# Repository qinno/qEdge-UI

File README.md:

# qEdge-UI

# Update
qEdge-UI supports now PICO2-W plattform (RP2350) with minimum changes as qEdge-UI++. Compilation now works in the Arduino 2.x.x IDE. LittleFS upload does not work in the moment, copy the files in /data to the SD-card, system copies it automagically to LittleFS on the first start. 

# About

This project is an example of use of what can be achieved with free/libre and open source software and free/libre and open source tools in a professional proceeding. 
In contrast to the generally accepted approach of commercial companies, the development results of this project (hardware and mechanical design, as well as software source code) are also available under an open source licence.

Based on the Raspberry Pi Pico (2), we have created a design that can be used as a starting point for further development. In order to keep things as simple as possible we use the Arduino platform.

Key hardware features of **qEdge-UI (qEdge-UI++)**:

- Raspberry Pi Pico RP2040 (2350)
- Dual-Core ARM Cortex M0+ CPU @133 MHz (ARM Cortex M33 @150 MHz or RISC-V)
- 264KB SRAM and 2MB Flash (520 KB / 4MB)
- WiFi + Bluetooth (Pico-W/Pico2-W)
- USB interface and power supply
- additional 12/24 VDC supply
- 3,2" TFT-Display 320x240 with resistive touch
- 4x1 keypad
- expansion connector for UART, I²C, GPIO, ADC
- RS-485 Interface
- Micro-SD-card slot
- LoRa module with stable SMA connector
- RTC with ultracap buffer
- Buzzer
- RGB-LEDs for signalling
- Raspberry Pi 3b/4b connectable (optional, not tested)

# Getting Started

### Electronics

To get started you will need the qEdge-UI electronic boards (main and display adapter). [We provide the full KiCad project here.](Electronics)

### Software

To get started with the software development you need a PC with:

* preinstalled Windows 7 or newer (64Bit), Linux (32/64Bit) or MacOS 10.10 newer
* An Arduino IDE 1.8.x including USB Driver support
* Addional you can use our qEdge-UI examples and libraries as a starting point for your own software development or you can download the precompiled UFS binaries of our qEdge-UI examples. [Here](Software) you can find the sources and installation guideline.

### Mechanics

To create the nice looking electronic box above you need a 3D printer [and the mechanics](Mechanics)

## qEdge-UI Hardware Test App functionality

The main objective of the qEdge-UI HwTestApp software is to check the functionality of the hardware.

* Touch - check precision of touch screen
* Slideshow - show PNG files on SD-Card (micro)
* UART - Test UART1 (RX/TX)
* RS-485 - Test UART2 connected to RS-485 driver (RX/TX)
* Micro-SD-card - check SD-card presence and list files on SD-card
* LittleFS - list, copy, rename and delete files in the filesystem
* LoRa - send/receive LoRa messages
* WiFi - scan and log in a network for receiving NTP time information
* GAME - space shooters clone to show performance
* Info - show system infos
* Keyboard - keyboard emulation
* Settings - set RGB preferences and backlight, test Buzzer

# Roadmap

See the [open issues](https://github.com/qinno/qEdge-UI/issues) for a list of proposed features (and known issues).

# Contributing

First of all, thank you for taking the time to contribute! Contributions are what make the open source community such an amazing place to learn, inspire and create. Every contribution you make benefits everyone else and is **greatly appreciated**.

Please try to create bug reports that are:

- _Reproducible._ Include steps to reproduce the problem.
- _Specific._ Include as much detail as possible: which version, what environment, etc.
- _Unique._ Do not duplicate existing open issues.
- _Scoped to a Single Bug._ One bug per report.

# Use and Regulations

Please note that this is an engineering example and is not certified to European regulations such as CE and RED, so use it at your own risk. If you find this platform helpful, we can assist you in creating a production-ready and certified product.

# Known limitations

This project is at the moment not used in a commercial open source product, but can be used as a starting point for that purpose. Please fell free to contact us for more information.

# Support

Reach out to the maintainer at one of the following places:

- By email which is located at [qinno GmbH · GitHub](https://github.com/qinno)

# Licenses

This project is licensed under the following open source licenses:
* Electronics are under [**CERN-OHL-S V2**](https://ohwr.org/cern_ohl_s_v2.txt)
* Mechanics and Design are under [**CC-BY-NC-4.0**](https://creativecommons.org/licenses/by-nc/4.0/legalcode)
* Software Examples are under [**GPLv3**](https://www.gnu.org/licenses/gpl-3.0.en.html)
   
See corresponding Readme.md files in the folders Electronics, Mechanics and Software for more detailed information.

[Raspberry Pi is a trademark of Raspberry Pi Ltd](http://www.raspberrypi.com/)

# Acknowledgements

Thanks to our partners supporting this project:

* [Our Customer Varmeco for the generous donation of material](https://varmeco.de)

* Axel Isele for the mechanics design

* [Würth Elektronik for free samples for the very first prototypes](https://www.we-online.com/de)

* All qinno-colleagues for their commitment even in their spare time

Thanks also for these awesome resources that were used during the development of the **qEdge-UI**:

* [The KiCAD team for their great CAE tool](https://www.kicad.org/)
* [Earle F. Philhower, III for his Arduino library for the RP2040](https://github.com/earlephilhower/arduino-pico)
* [Bodmer for his versatile TFT-Library](https://github.com/Bodmer/TFT_eSPI)
* [Larry Bank for his PNG extension](https://github.com/bitbank2/PNGdec)
* [The Adafruit Industries Team for their RGB-LED library](https://github.com/adafruit/Adafruit_NeoPixel)
* [The Arduino team for their easy to use (now legacy) IDE](https://www.arduino.cc/en/software)
* [Sandeep Mistry for his handy LoRa library](https://github.com/sandeepmistry/arduino-LoRa)

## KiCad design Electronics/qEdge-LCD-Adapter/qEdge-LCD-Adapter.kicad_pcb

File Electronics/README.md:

# qEdge-UI electronics

In this directory you will find the complete electronic design in KiCAD.

### The main electronics

[in the directory qedge-UI](qEdge-UI)

### The display adapter board

 [in the directory qEdge-LCD-Adapter](qEdge-LCD-Adapter)

You need to glue the display to the adapter board with double-sided adhesive tape and connect it to the ZIF-connector.

For use with RaspBerry Pi Pico or Pico-W you need to close the Jumpers JP500 and JP501. After you have assembled both boards, you need to connect them with a ribbon cable.

Now screw the LCD display on top of the main board.

You can supply the unit via Micro-USB (5V) and/or via the Phoenix connectors with 12V/24V (mating connector Phoenix 1952267).

The RS-485 connector needs Phoenix mating connector 1952270 to fit.

Fingers crossed ...

# License

(C) 2023 qinno - this work is licensed under CERN-OHL-S
see https://ohwr.org/cern_ohl_s_v2.pdf for more information

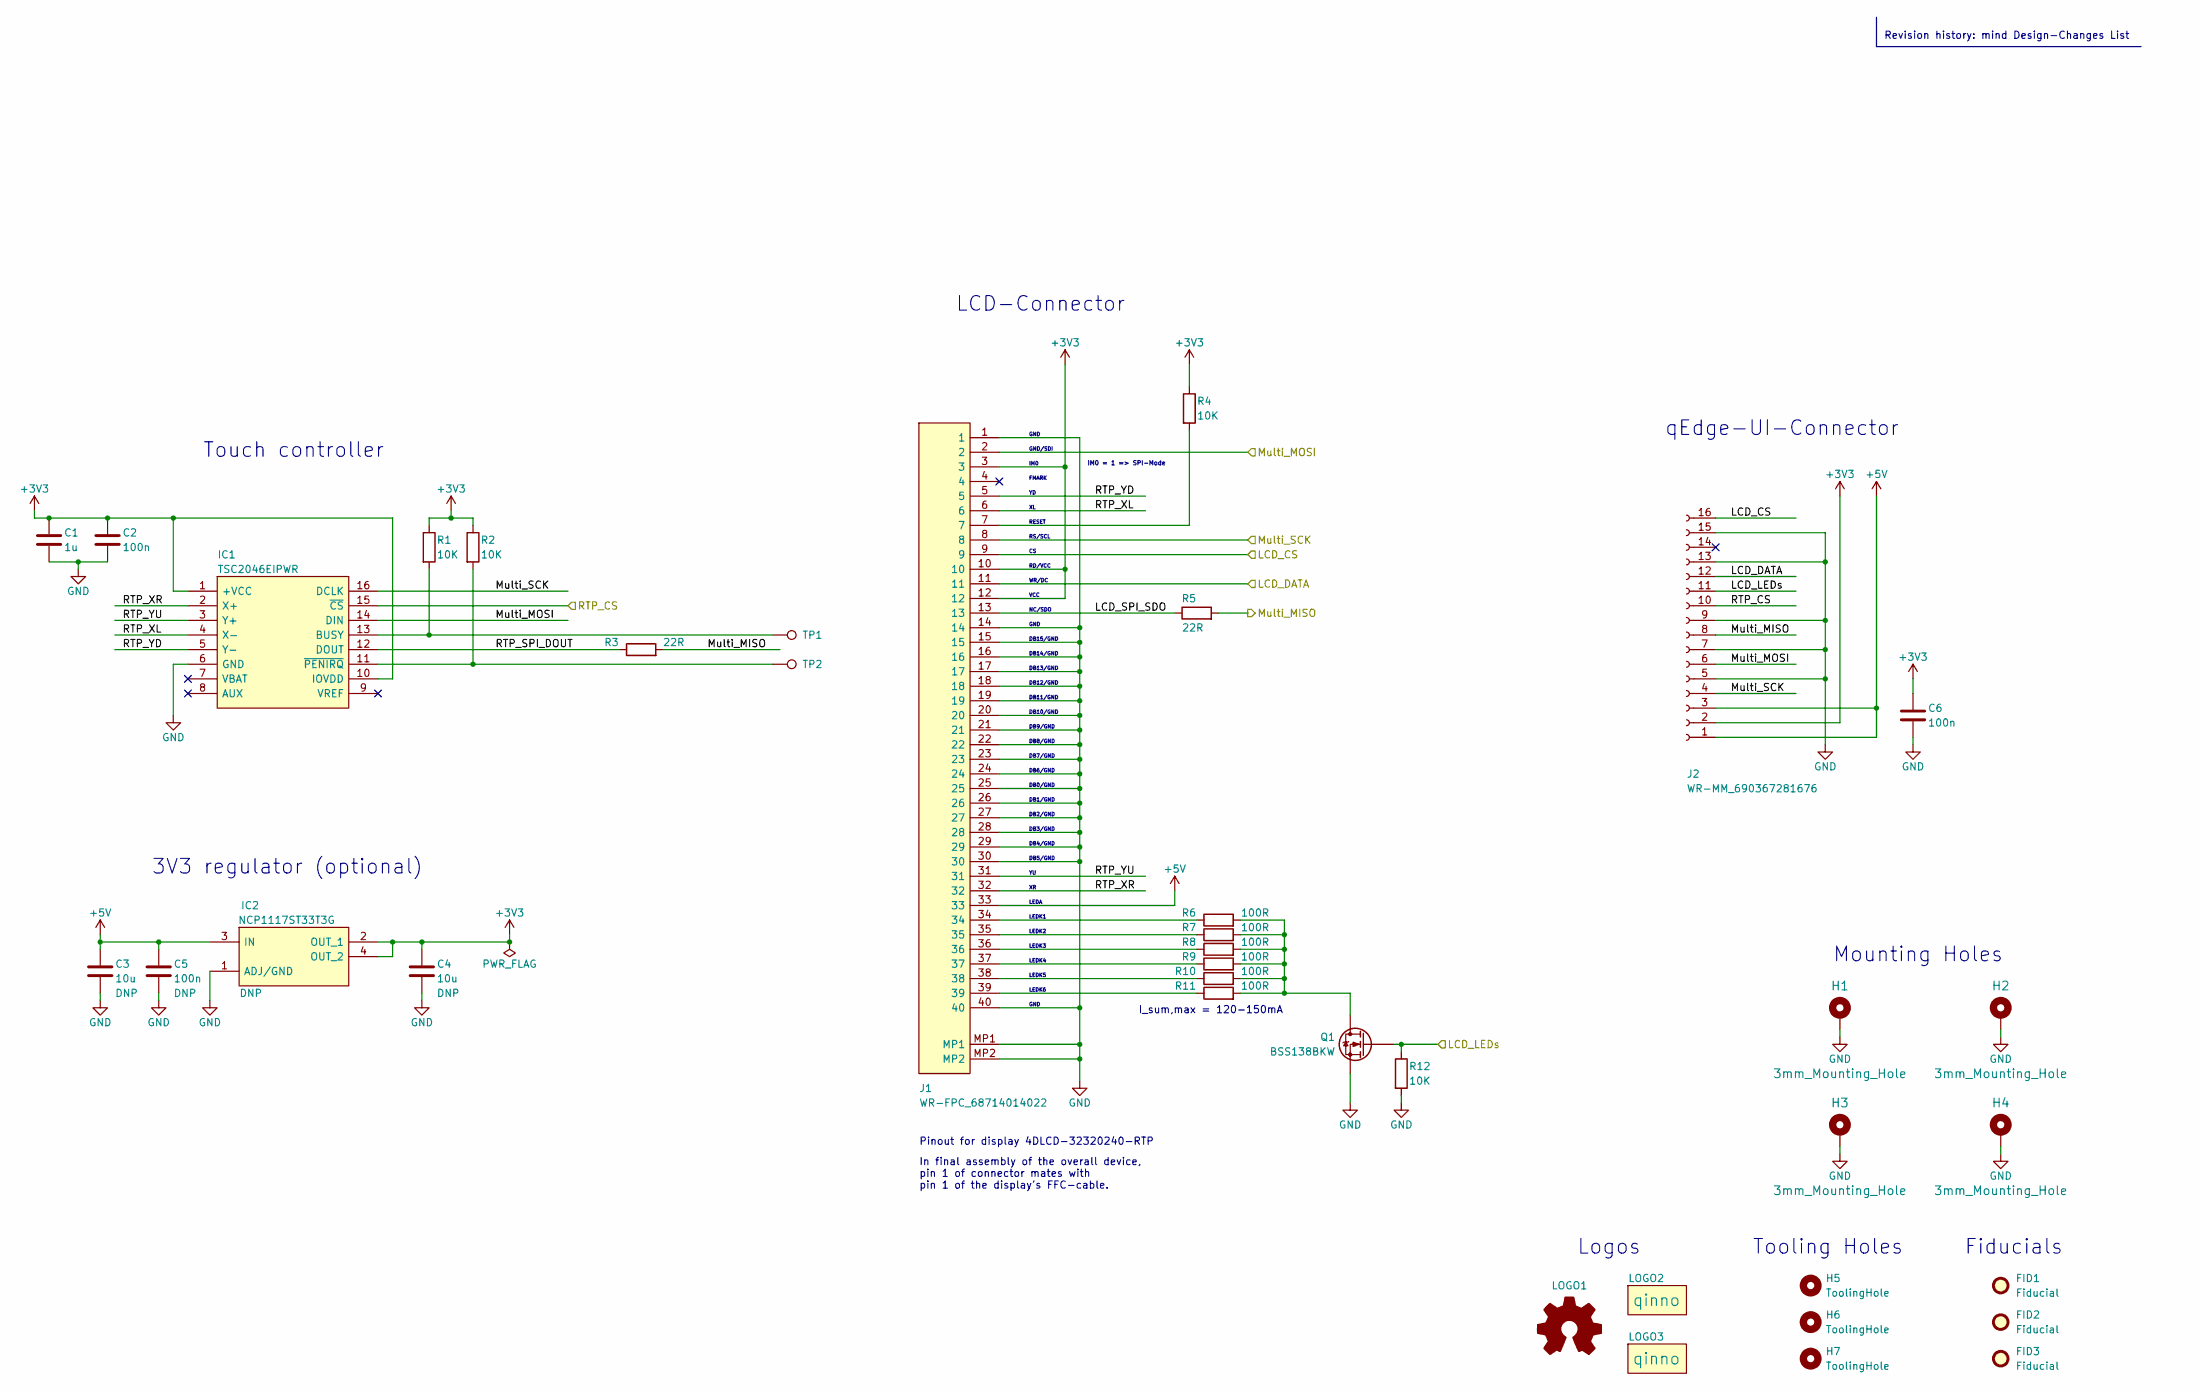
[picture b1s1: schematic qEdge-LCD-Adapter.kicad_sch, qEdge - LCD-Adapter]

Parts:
C1: 1u; C_0603_1608Metric
C2, C5, C6: 100n; C_0603_1608Metric
C3, C4: 10u; C_0603_1608Metric
FID1, FID2, FID3: Fiducial; Fiducial_1mm_Mask3mm
H1, H2, H3, H4: 3mm_Mounting_Hole; MountingHole_3.2mm_M3_DIN965_Pad
H5, H6, H7: ToolingHole; JLCSMT_ToolingHole
IC1: TSC2046EIPWR; SOP65P640X120-16N; Manufacturer_Part_Number TSC2046EIPWR
IC2: NCP1117ST33T3G; SOT230P700X180-4N; Manufacturer_Part_Number NCP1117ST33T3G
J1: WR-FPC_68714014022; Wuerth_WR-FPC_68714014022; Manufacturer_Part_Number 68714014022
J2: WR-MM_690367281676; Wuerth_WR-MM_690367281676; Manufacturer_Part_Number 690367281676
LOGO1: Logo_Open_Hardware_Small; OSHW-Logo2_9.8x8mm_Copper
LOGO2, LOGO3: qinno; Logo-qinno-2
Q1: BSS138BKW; SOT-323_SC-70; Manufacturer_Part_Number BSS138BKW,115
R1, R2, R4, R12: 10K; R_0603_1608Metric
R3, R5: 22R; R_0603_1608Metric
R6, R7, R8, R9, R10, R11: 100R; R_0603_1608Metric
TP1, TP2: TestPoint; TestPoint_Pad_D1.0mm

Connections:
+3V3: C1.1, C2.1, C4.1, C6.1, IC1.1 (+VCC), IC1.10 (IOVDD), IC2.2 (OUT_1), IC2.4 (OUT_2), J1.3, J1.10, J1.12, J2.2, R1.1, R2.1, R4.1
+5V: C3.1, C5.1, IC2.3 (IN), J1.33, J2.1, J2.3
/LCD_CS: J1.9, J2.16
/LCD_DATA: J1.11, J2.12
/LCD_LEDs: J2.11, Q1.1 (G), R12.1
/LCD_SPI_SDO: J1.13, R5.1
/Multi_MISO: J2.8, R3.2, R5.2
/Multi_MOSI: IC1.14 (DIN), J1.2, J2.6
/Multi_SCK: IC1.16 (DCLK), J1.8, J2.4
/RTP_CS: IC1.15 (~CS), J2.10
/RTP_SPI_DOUT: IC1.12 (DOUT), R3.1
/RTP_XL: IC1.4 (X-), J1.6
/RTP_XR: IC1.2 (X+), J1.32
/RTP_YD: IC1.5 (Y-), J1.5
/RTP_YU: IC1.3 (Y+), J1.31
GND: C1.2, C2.2, C3.2, C4.2, C5.2, C6.2, H1.1, H2.1, H3.1, H4.1, IC1.6 (GND), IC2.1 (ADJ/GND), J1.1, J1.14, J1.15, J1.16, J1.17, J1.18, J1.19, J1.20, J1.21, J1.22, J1.23, J1.24, J1.25, J1.26, J1.27, J1.28, J1.29, J1.30, J1.40, J1.MP1, J1.MP2, J2.5, J2.7, J2.9, J2.13, J2.15, Q1.2 (S), R12.2
unnamed: IC1.11 (~PENIRQ), R2.2, TP2.1
unnamed: IC1.13 (BUSY), R1.2, TP1.1
unnamed: J1.7, R4.2
unnamed: J1.34, R6.1
unnamed: J1.35, R7.1
unnamed: J1.36, R8.1
unnamed: J1.37, R9.1
unnamed: J1.38, R10.1
unnamed: J1.39, R11.1
unnamed: Q1.3 (D), R6.2, R7.2, R8.2, R9.2, R10.2, R11.2

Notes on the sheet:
LEDK3
GND
DB3/GND
DB9/GND
LEDK4
DB14/GND
LEDK2
DB5/GND
WR/DC
FMARK
Tooling Holes
IM0
LEDA
Pinout for display 4DLCD-32320240-RTP
RS/SCL
DB1/GND
LEDK5
RESET
DB10/GND
RD/VCC
DB8/GND
NC/SDO
DB0/GND
LEDK1
I_sum,max = 120-150mA
LEDK6
Logos
DB2/GND
DB11/GND
DB4/GND
qEdge-UI-Connector
DB7/GND
DB13/GND
LCD-Connector
DB15/GND
3V3 regulator (optional)
GND/SDI
Mounting Holes
Revision history: mind Design-Changes List
Touch controller

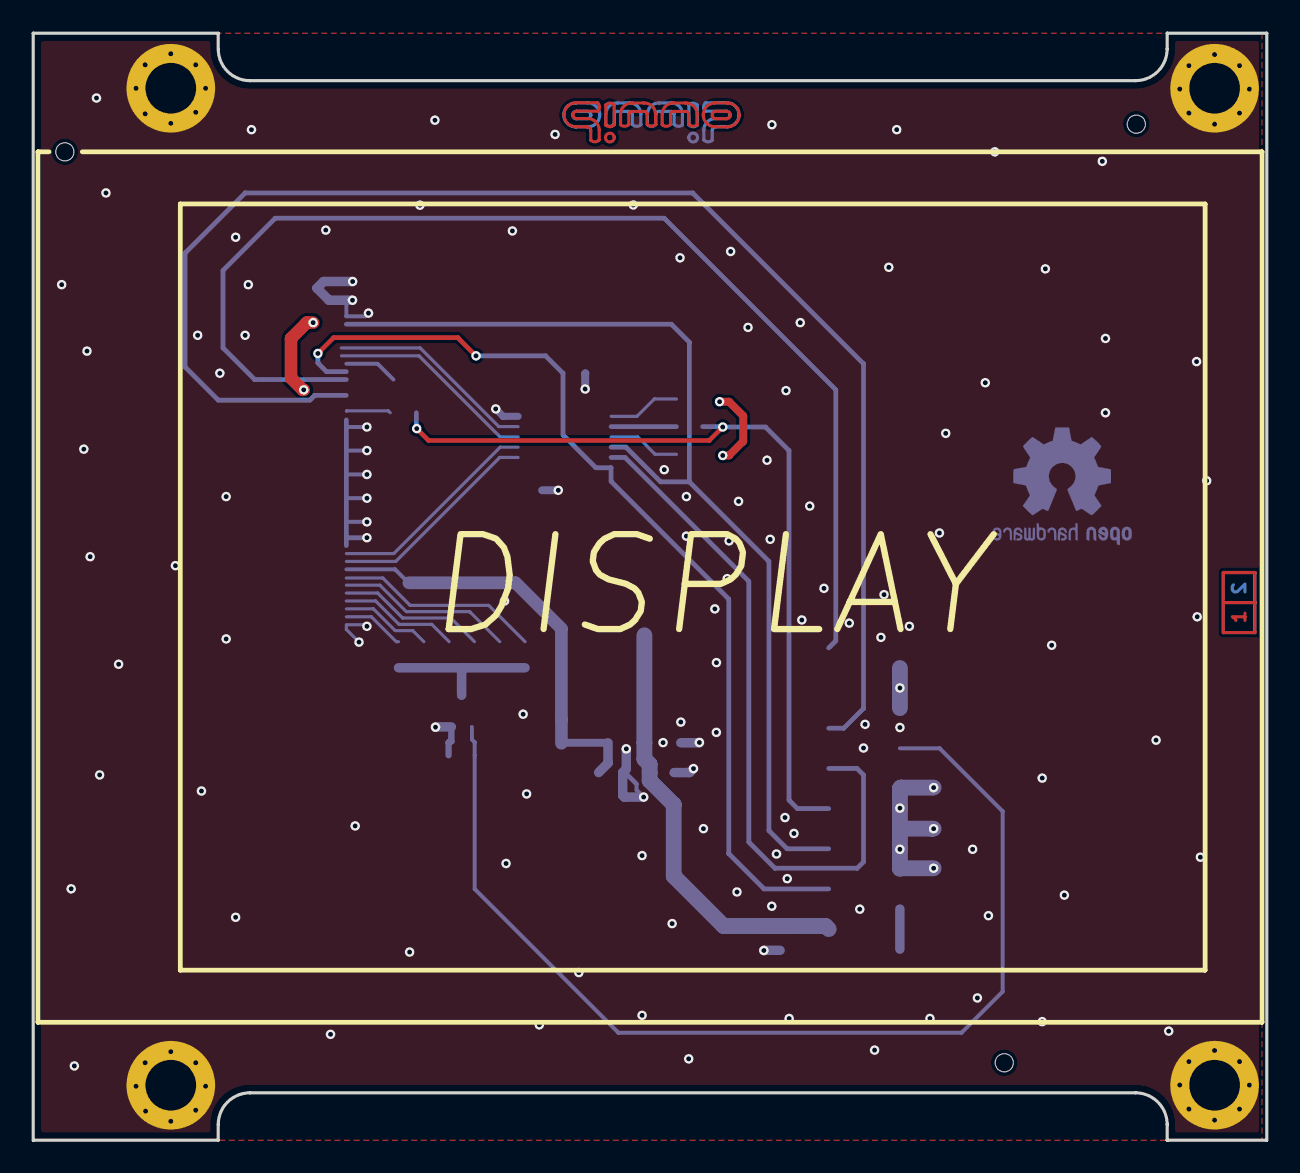
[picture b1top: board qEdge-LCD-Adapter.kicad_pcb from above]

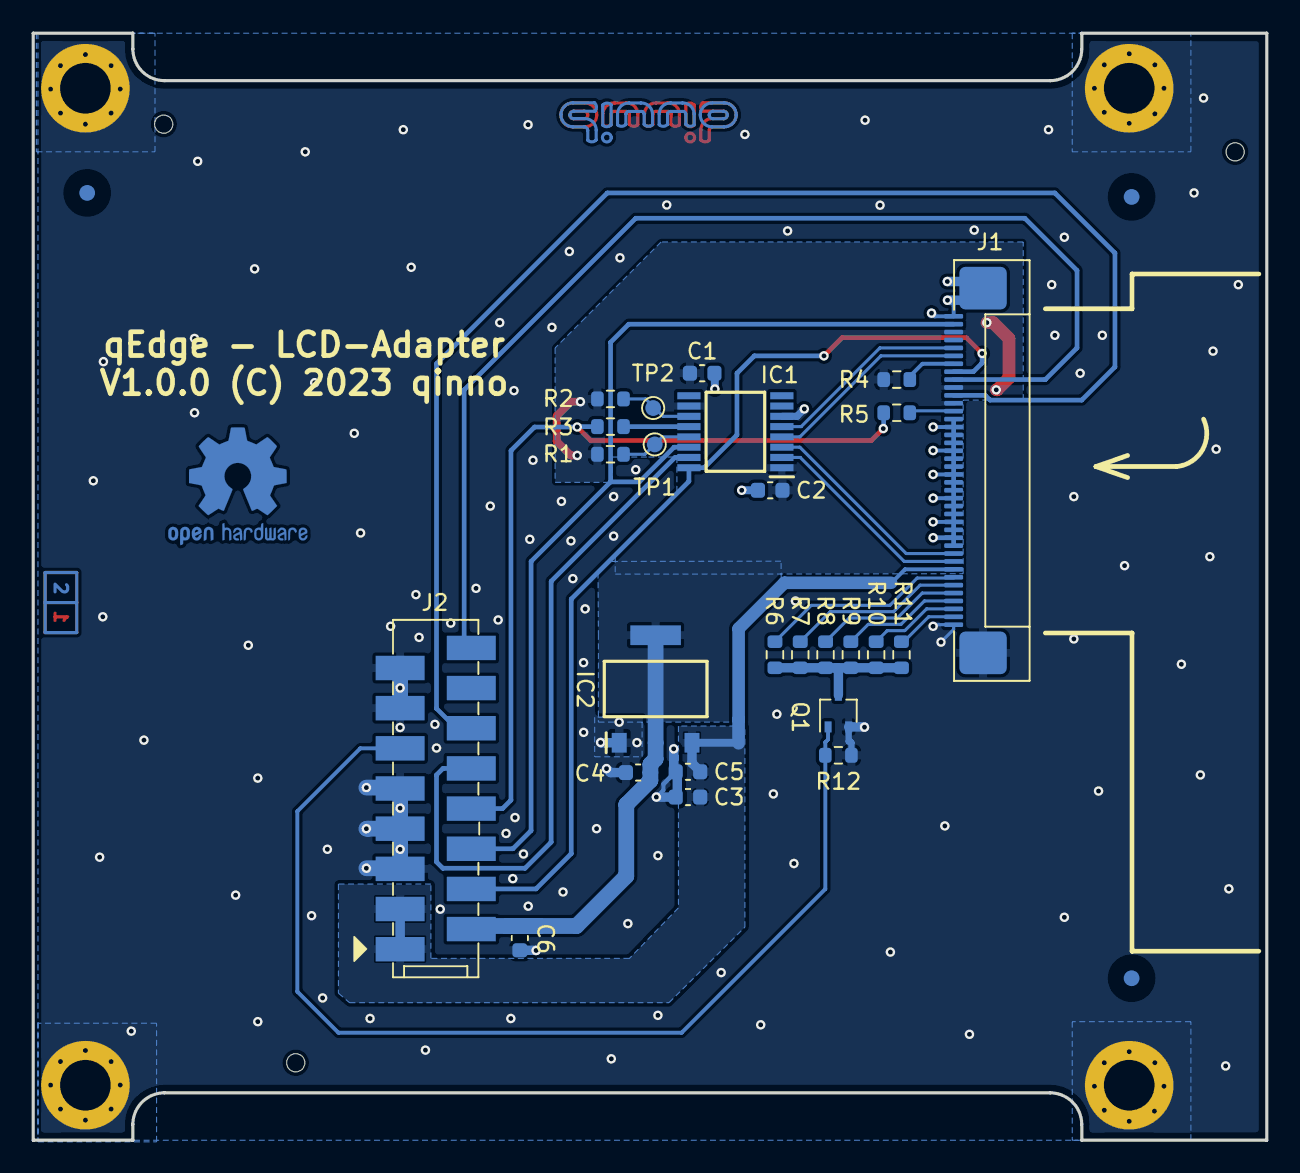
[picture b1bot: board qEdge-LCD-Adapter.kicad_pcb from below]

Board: 2 copper layers, 78.0 x 70.0 mm, 38 parts (30 on the bottom side), 26 nets.

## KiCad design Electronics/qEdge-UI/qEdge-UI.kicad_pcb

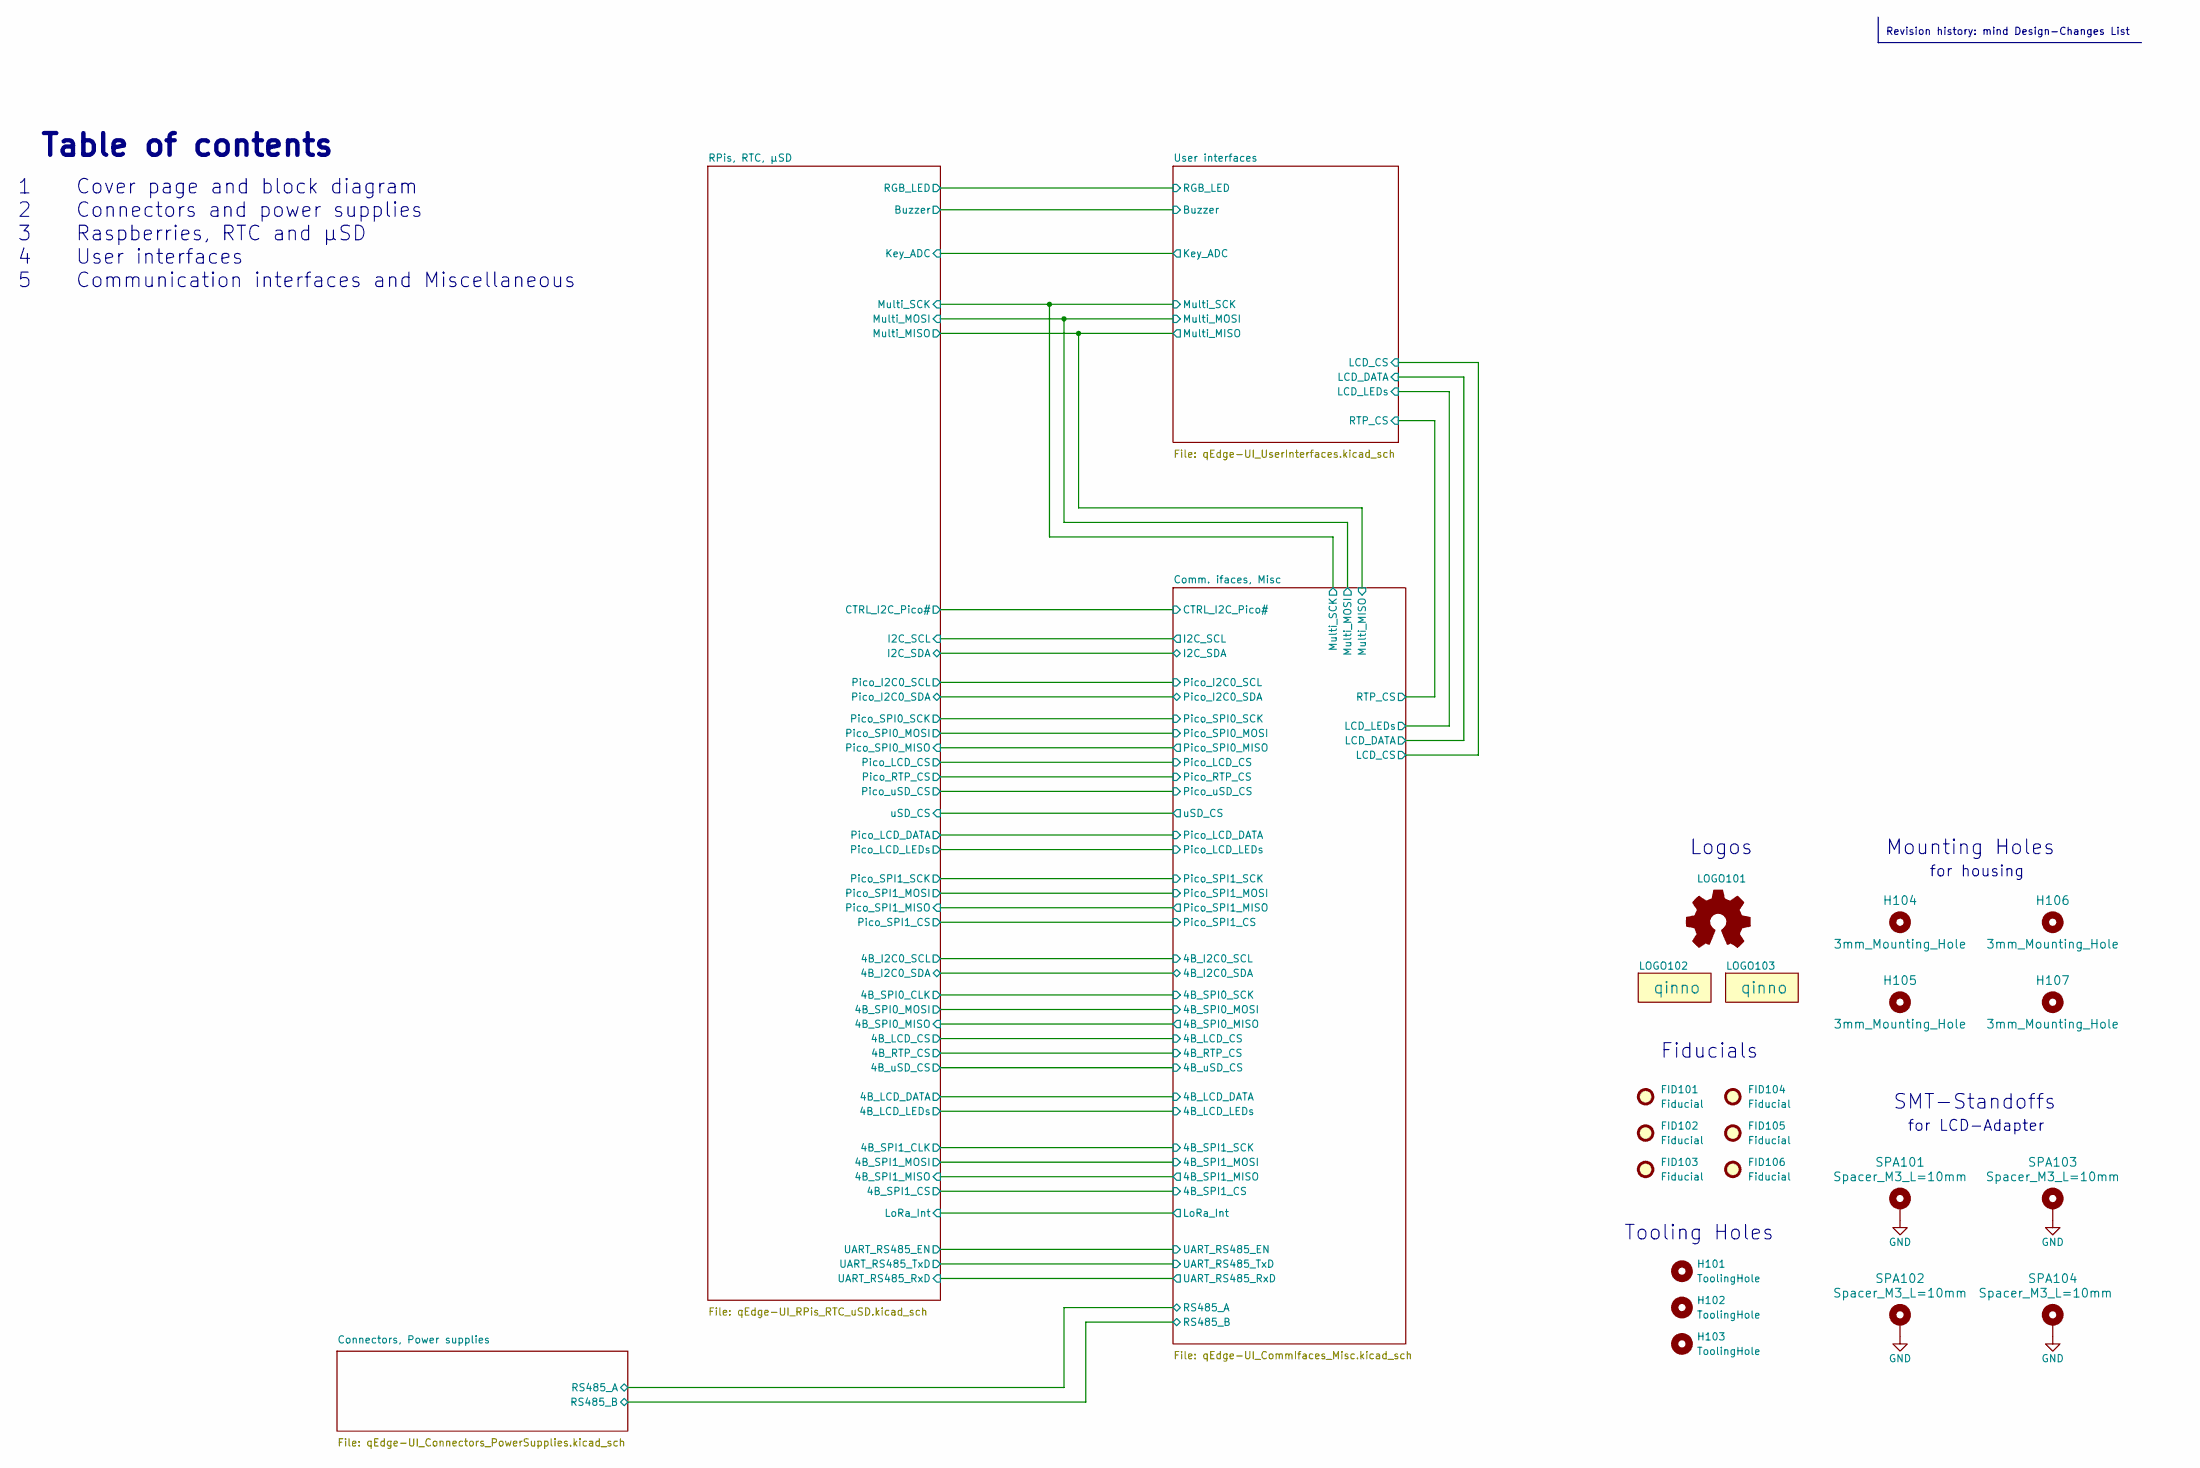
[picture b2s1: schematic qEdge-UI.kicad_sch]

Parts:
FID101, FID102, FID103, FID104, FID105, FID106: Fiducial; Fiducial_1mm_Mask3mm
H101, H102, H103: ToolingHole; JLCSMT_ToolingHole
H104, H105, H106, H107: 3mm_Mounting_Hole; NPTH_3mm_ID
LOGO101: Logo_Open_Hardware_Small; OSHW-Logo2_9.8x8mm_Copper
LOGO102, LOGO103: qinno; Logo-qinno-2
SPA101, SPA102, SPA103, SPA104: Spacer_M3_L=10mm; Mounting_Wuerth_WA-SMSI-M3_H10mm_9774100360; Manufacturer_Part_Number 9774100360

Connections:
GND: SPA101.1, SPA102.1, SPA103.1, SPA104.1; also elsewhere on the board

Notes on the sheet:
Logos
Mounting Holes
SMT-Standoffs
Tooling Holes
Revision history: mind Design-Changes List
for LCD-Adapter
Table of contents
for housing
1 Cover page and block diagram 2 Connectors and power supplies 3 Raspberries, RTC and µSD 4 User interfaces 5 Communication interfaces and Miscellaneous
Fiducials

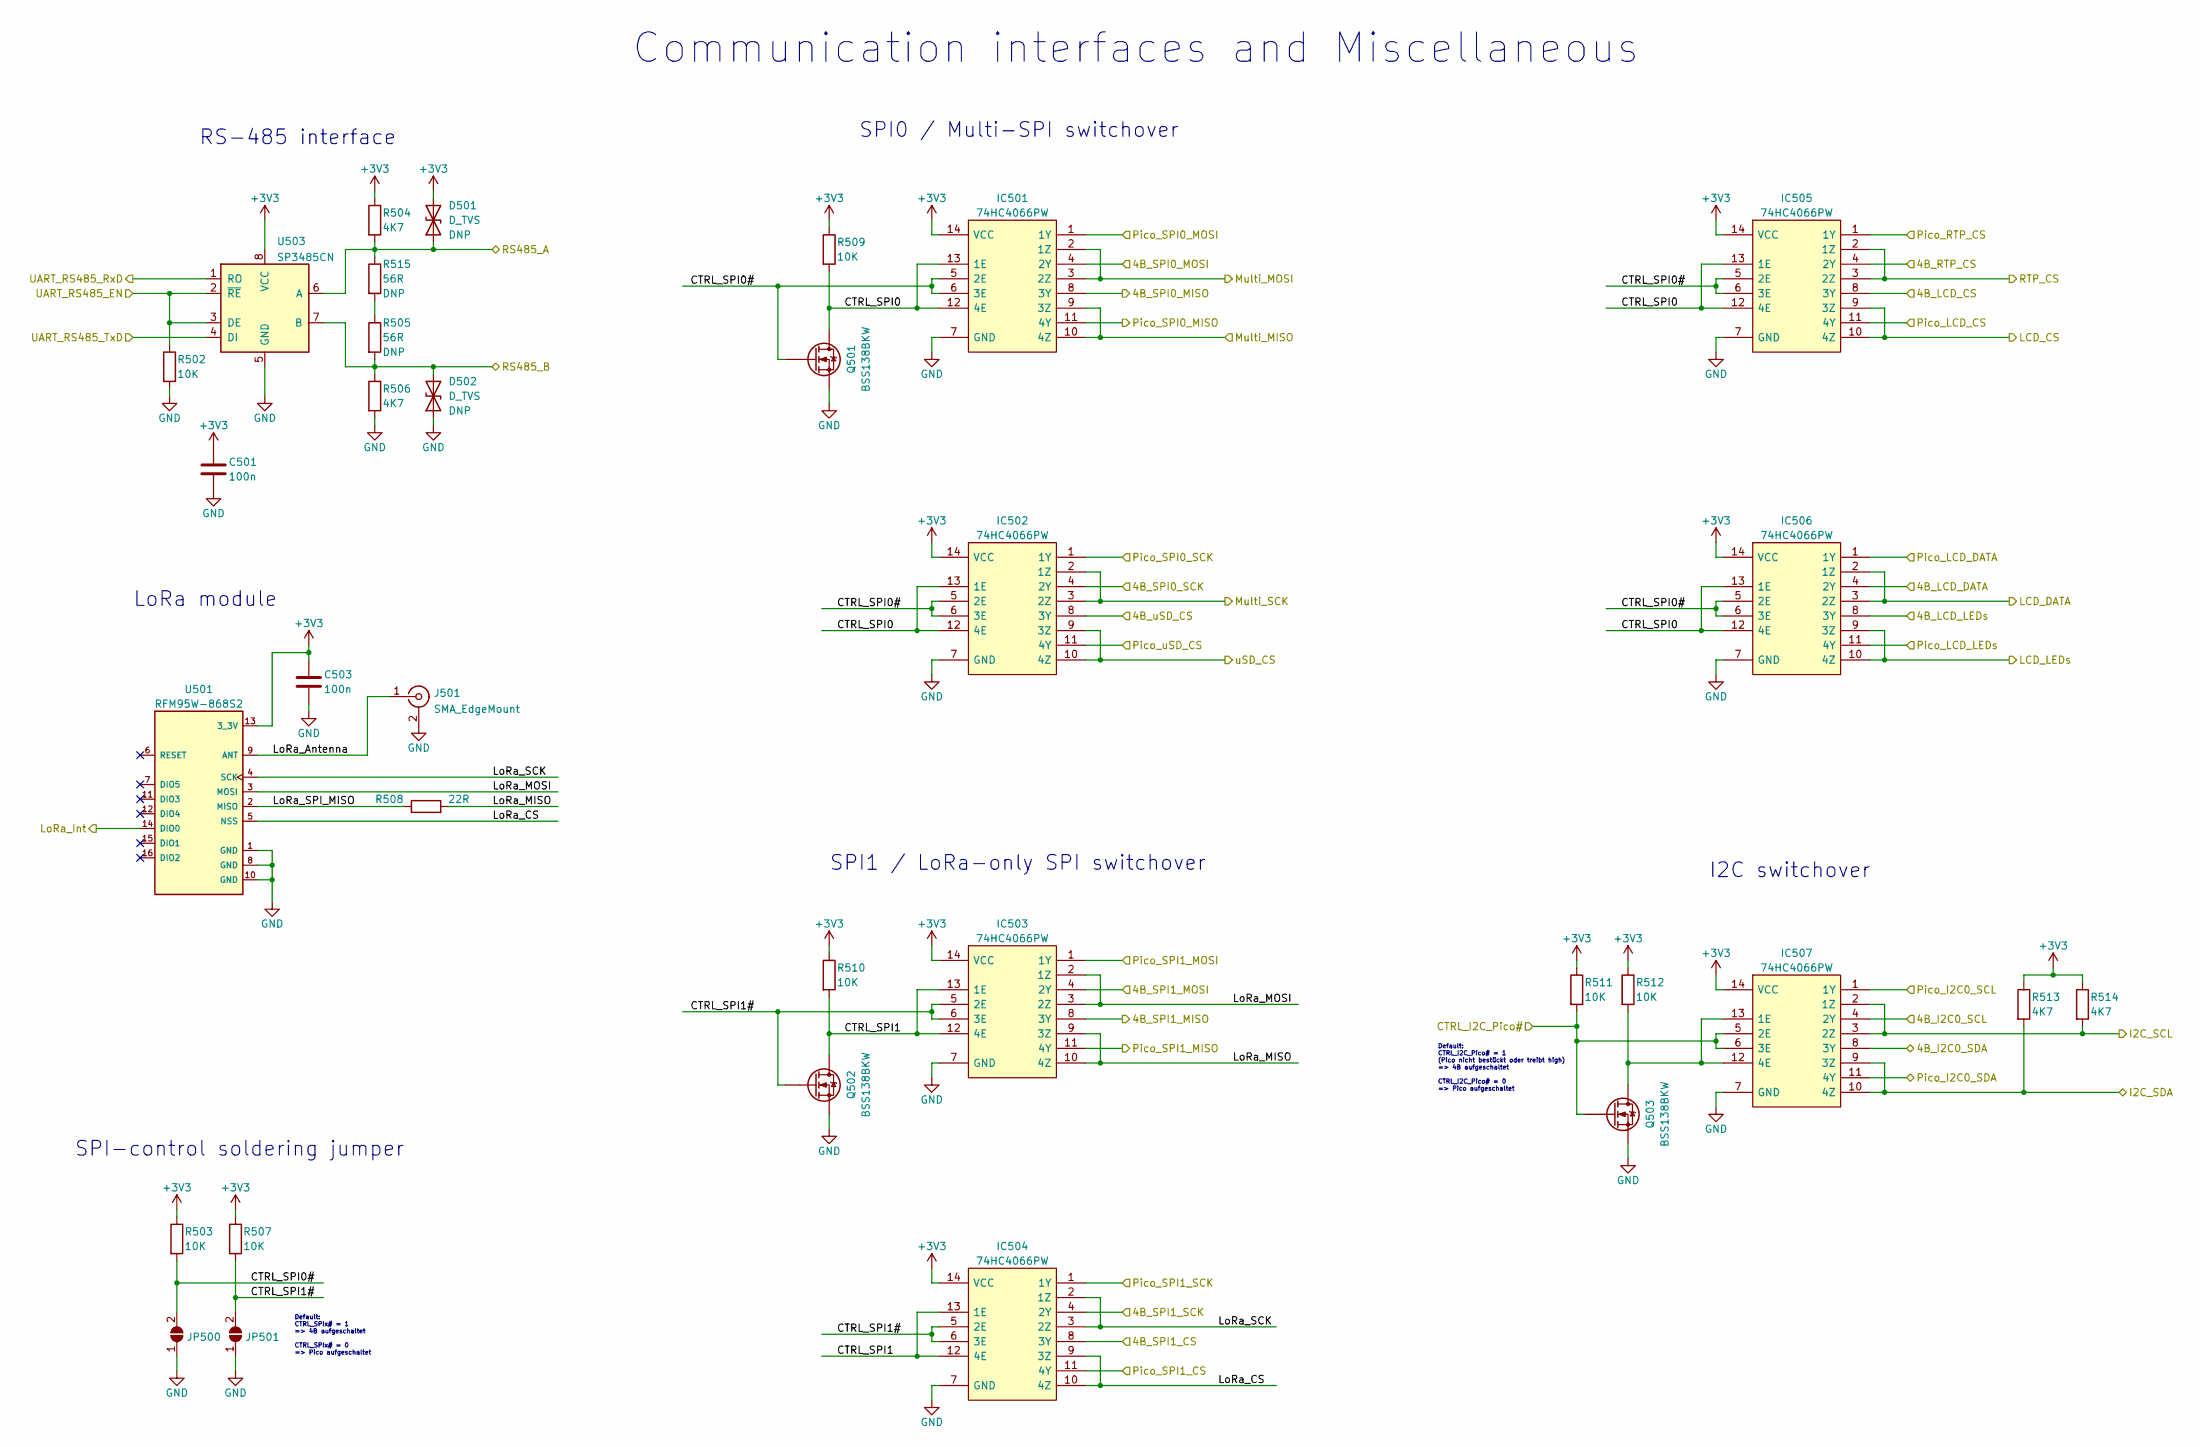
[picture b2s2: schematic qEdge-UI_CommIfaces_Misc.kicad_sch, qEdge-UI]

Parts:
C501, C503: 100n; C_0603_1608Metric
D501, D502: D_TVS; D_SMA_bipolar
IC501, IC502, IC503, IC504, IC505, IC506, IC507: 74HC4066PW; SOP65P640X110-14N; Manufacturer_Part_Number 74HC4066PW,118
J501: SMA_EdgeMount; Samtec_SMA-J-P-X-ST-EM1; Manufacturer_Part_Number SMA-J-P-H-ST-EM1
JP500, JP501: SolderJumper_2_Open; SolderJumper-2_P1.3mm_Open_TrianglePad1.0x1.5mm
Q501, Q502, Q503: BSS138BKW; SOT-323_SC-70; Manufacturer_Part_Number BSS138BKW,115
R502, R503, R507, R509, R510, R511, R512: 10K; R_0603_1608Metric
R504, R506, R513, R514: 4K7; R_0603_1608Metric
R505, R515: 56R; R_0603_1608Metric
R508: 22R; R_0603_1608Metric
U501: RFM95W-868S2; HopeRF_RFM95W-868S2; Manufacturer_Part_Number RFM95W-868S2
U503: SP3485CN; SOIC-8_3.9x4.9mm_P1.27mm; Manufacturer_Part_Number SP3485CN-L/TR

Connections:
+3V3: C501.1, C503.1, D501.2 (A2), IC501.14 (VCC), IC502.14 (VCC), IC503.14 (VCC), IC504.14 (VCC), IC505.14 (VCC), IC506.14 (VCC), IC507.14 (VCC), R503.1, R504.1, R507.1, R509.1, R510.1, R511.1, R512.1, R513.1, R514.1, U501.13 (3_3V), U503.8 (VCC); also elsewhere on the board
/Comm. ifaces, Misc/4B_I2C0_SCL: IC507.4 (2Y); also elsewhere on the board
/Comm. ifaces, Misc/4B_I2C0_SDA: IC507.8 (3Y); also elsewhere on the board
/Comm. ifaces, Misc/4B_LCD_CS: IC505.8 (3Y); also elsewhere on the board
/Comm. ifaces, Misc/4B_LCD_DATA: IC506.4 (2Y); also elsewhere on the board
/Comm. ifaces, Misc/4B_LCD_LEDs: IC506.8 (3Y); also elsewhere on the board
/Comm. ifaces, Misc/4B_RTP_CS: IC505.4 (2Y); also elsewhere on the board
/Comm. ifaces, Misc/4B_SPI0_MISO: IC501.8 (3Y); also elsewhere on the board
/Comm. ifaces, Misc/4B_SPI0_MOSI: IC501.4 (2Y); also elsewhere on the board
/Comm. ifaces, Misc/4B_SPI0_SCK: IC502.4 (2Y); also elsewhere on the board
/Comm. ifaces, Misc/4B_SPI1_CS: IC504.8 (3Y); also elsewhere on the board
/Comm. ifaces, Misc/4B_SPI1_MISO: IC503.8 (3Y); also elsewhere on the board
/Comm. ifaces, Misc/4B_SPI1_MOSI: IC503.4 (2Y); also elsewhere on the board
/Comm. ifaces, Misc/4B_SPI1_SCK: IC504.4 (2Y); also elsewhere on the board
/Comm. ifaces, Misc/4B_uSD_CS: IC502.8 (3Y); also elsewhere on the board
/Comm. ifaces, Misc/CTRL_SPI0: IC501.12 (4E), IC501.13 (1E), IC502.12 (4E), IC502.13 (1E), IC505.12 (4E), IC505.13 (1E), IC506.12 (4E), IC506.13 (1E), Q501.3 (D), R509.2
/Comm. ifaces, Misc/CTRL_SPI0#: IC501.5 (2E), IC501.6 (3E), IC502.5 (2E), IC502.6 (3E), IC505.5 (2E), IC505.6 (3E), IC506.5 (2E), IC506.6 (3E), JP500.2 (B), Q501.1 (G), R503.2
/Comm. ifaces, Misc/CTRL_SPI1: IC503.12 (4E), IC503.13 (1E), IC504.12 (4E), IC504.13 (1E), Q502.3 (D), R510.2
/Comm. ifaces, Misc/CTRL_SPI1#: IC503.5 (2E), IC503.6 (3E), IC504.5 (2E), IC504.6 (3E), JP501.2 (B), Q502.1 (G), R507.2
/Comm. ifaces, Misc/I2C_SCL: IC507.2 (1Z), IC507.3 (2Z), R514.2; also elsewhere on the board
/Comm. ifaces, Misc/I2C_SDA: IC507.9 (3Z), IC507.10 (4Z), R513.2; also elsewhere on the board
/Comm. ifaces, Misc/LCD_CS: IC505.9 (3Z), IC505.10 (4Z); also elsewhere on the board
/Comm. ifaces, Misc/LCD_DATA: IC506.2 (1Z), IC506.3 (2Z); also elsewhere on the board
/Comm. ifaces, Misc/LCD_LEDs: IC506.9 (3Z), IC506.10 (4Z); also elsewhere on the board
/Comm. ifaces, Misc/LoRa_Antenna: J501.1 (In), U501.9 (ANT)
/Comm. ifaces, Misc/LoRa_CS: IC504.9 (3Z), IC504.10 (4Z), U501.5 (NSS)
/Comm. ifaces, Misc/LoRa_MISO: IC503.9 (3Z), IC503.10 (4Z), R508.2
/Comm. ifaces, Misc/LoRa_MOSI: IC503.2 (1Z), IC503.3 (2Z), U501.3 (MOSI)
/Comm. ifaces, Misc/LoRa_SCK: IC504.2 (1Z), IC504.3 (2Z), U501.4 (SCK)
/Comm. ifaces, Misc/LoRa_SPI_MISO: R508.1, U501.2 (MISO)
/Comm. ifaces, Misc/Multi_MISO: IC501.9 (3Z), IC501.10 (4Z); also elsewhere on the board
/Comm. ifaces, Misc/Multi_MOSI: IC501.2 (1Z), IC501.3 (2Z); also elsewhere on the board
/Comm. ifaces, Misc/Multi_SCK: IC502.2 (1Z), IC502.3 (2Z); also elsewhere on the board
/Comm. ifaces, Misc/Pico_LCD_CS: IC505.11 (4Y); also elsewhere on the board
/Comm. ifaces, Misc/Pico_RTP_CS: IC505.1 (1Y); also elsewhere on the board
/Comm. ifaces, Misc/Pico_SPI0_MISO: IC501.11 (4Y); also elsewhere on the board
/Comm. ifaces, Misc/Pico_SPI0_MOSI: IC501.1 (1Y); also elsewhere on the board
/Comm. ifaces, Misc/Pico_SPI0_SCK: IC502.1 (1Y); also elsewhere on the board
/Comm. ifaces, Misc/Pico_SPI1_CS: IC504.11 (4Y); also elsewhere on the board
/Comm. ifaces, Misc/Pico_SPI1_MISO: IC503.11 (4Y); also elsewhere on the board
/Comm. ifaces, Misc/Pico_SPI1_MOSI: IC503.1 (1Y); also elsewhere on the board
/Comm. ifaces, Misc/Pico_SPI1_SCK: IC504.1 (1Y); also elsewhere on the board
/Comm. ifaces, Misc/Pico_uSD_CS: IC502.11 (4Y); also elsewhere on the board
/Comm. ifaces, Misc/RS485_A: D501.1 (A1), R504.2, R515.1, U503.6 (A); also elsewhere on the board
/Comm. ifaces, Misc/RS485_B: D502.2 (A2), R505.2, R506.1, U503.7 (B); also elsewhere on the board
/Comm. ifaces, Misc/RTP_CS: IC505.2 (1Z), IC505.3 (2Z); also elsewhere on the board
/Comm. ifaces, Misc/UART_RS485_EN: R502.1, U503.2 (~RE), U503.3 (DE); also elsewhere on the board
/Comm. ifaces, Misc/UART_RS485_RxD: U503.1 (RO); also elsewhere on the board
/Comm. ifaces, Misc/UART_RS485_TxD: U503.4 (DI); also elsewhere on the board
/Comm. ifaces, Misc/uSD_CS: IC502.9 (3Z), IC502.10 (4Z); also elsewhere on the board
/RPis, RTC, µSD/CTRL_I2C_Pico#: IC507.5 (2E), IC507.6 (3E), Q503.1 (G), R511.2; also elsewhere on the board
/RPis, RTC, µSD/LoRa_Int: U501.14 (DIO0); also elsewhere on the board
/RPis, RTC, µSD/Pico_I2C0_SCL: IC507.1 (1Y); also elsewhere on the board
/RPis, RTC, µSD/Pico_I2C0_SDA: IC507.11 (4Y); also elsewhere on the board
/RPis, RTC, µSD/Pico_LCD_DATA: IC506.1 (1Y); also elsewhere on the board
/RPis, RTC, µSD/Pico_LCD_LEDs: IC506.11 (4Y); also elsewhere on the board
GND: C501.2, C503.2, D502.1 (A1), IC501.7 (GND), IC502.7 (GND), IC503.7 (GND), IC504.7 (GND), IC505.7 (GND), IC506.7 (GND), IC507.7 (GND), J501.2 (Ext), JP500.1 (A), JP501.1 (A), Q501.2 (S), Q502.2 (S), Q503.2 (S), R502.2, R506.2, U501.1 (GND), U501.8 (GND), U501.10 (GND), U503.5 (GND); also elsewhere on the board
unnamed: IC507.12 (4E), IC507.13 (1E), Q503.3 (D), R512.2
unnamed: R505.1, R515.2

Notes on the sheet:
RS-485 interface
Default: CTRL_I2C_Pico# = 1 (Pico nicht bestückt oder treibt high) => 4B aufgeschaltet CTRL_I2C_Pico# = 0 => Pico aufgeschaltet
I2C switchover
Communication interfaces and Miscellaneous
SPI0 / Multi-SPI switchover
LoRa module
Default: CTRL_SPIx# = 1 => 4B aufgeschaltet CTRL_SPIx# = 0 => Pico aufgeschaltet
SPI-control soldering jumper
SPI1 / LoRa-only SPI switchover

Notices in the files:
Electronics/qEdge-LCD-Adapter/qEdge-LCD-Adapter.kicad_pcb:
V1.0.0 (C) 2023 qinno
